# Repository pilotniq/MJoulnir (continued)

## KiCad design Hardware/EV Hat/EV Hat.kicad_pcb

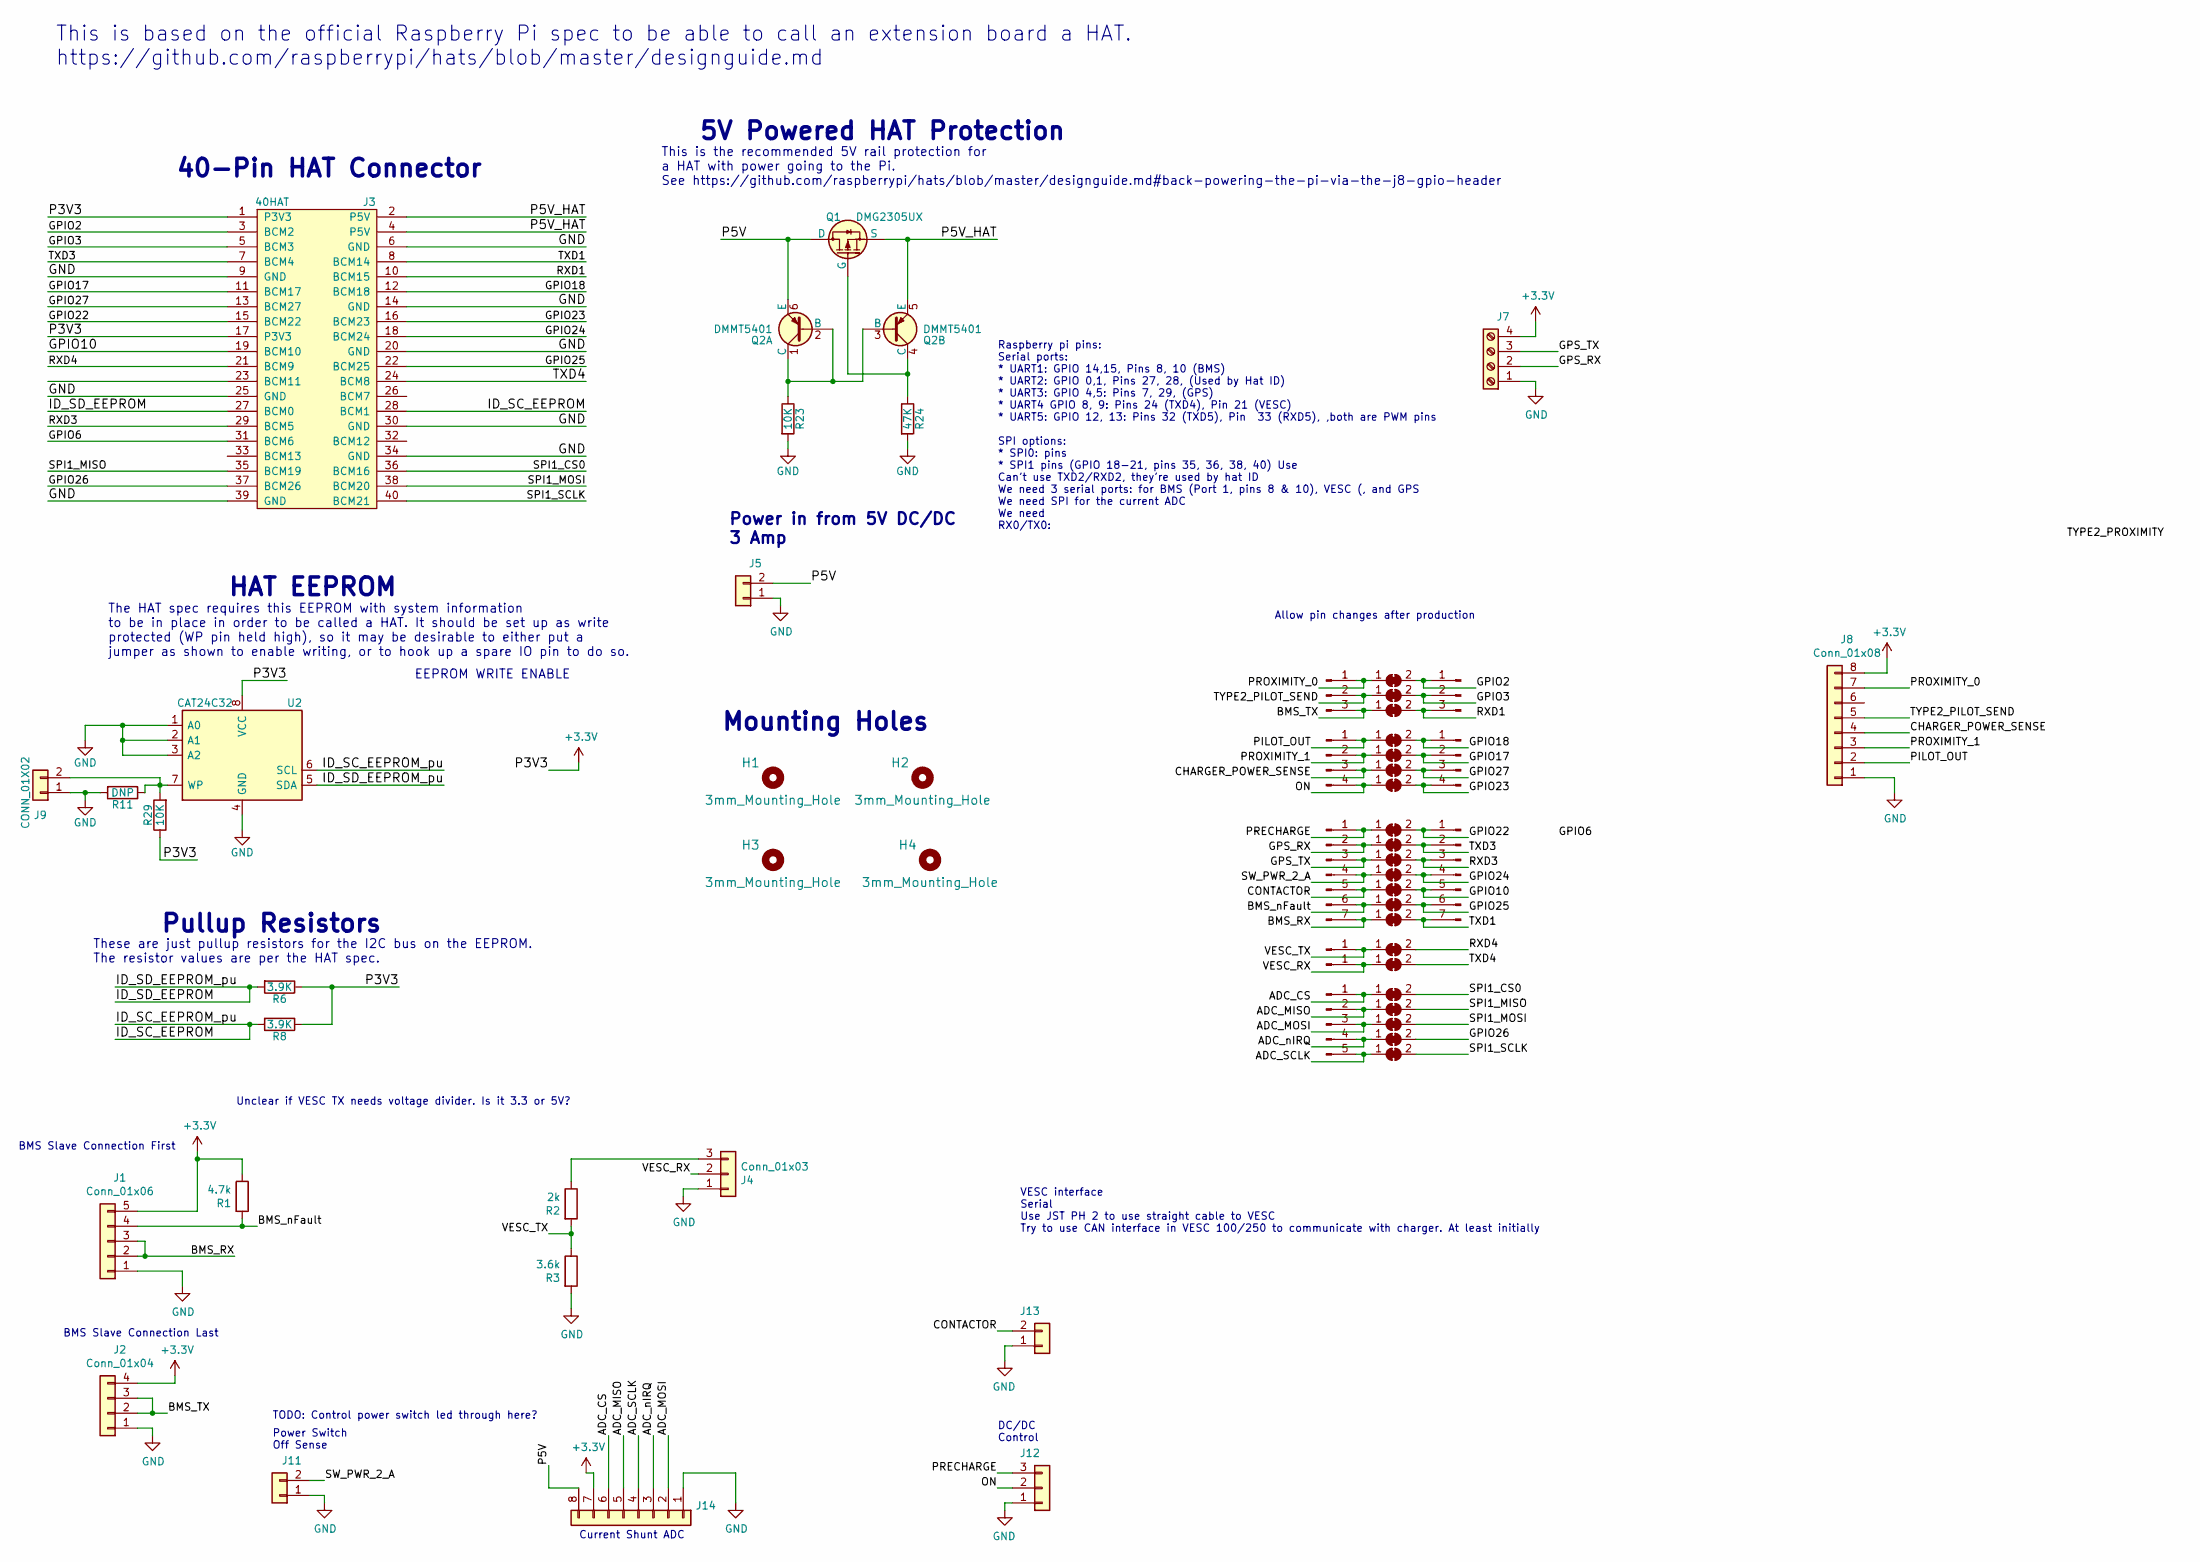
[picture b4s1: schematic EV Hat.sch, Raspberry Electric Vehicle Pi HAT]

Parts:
H1, H2, H3, H4: 3mm_Mounting_Hole; NPTH_3mm_ID
J1: Conn_01x06; CON-MOLEX-CGRIDIII-2x3-0901303206
J2: Conn_01x04; CON-MOLEX-CGRIDIII-1x4-0901361204
J3: 40HAT; PinSocket_2x20_P2.54mm_Vertical
J4, J12: Conn_01x03; CON-MOLEX-CGRIDIII-1x3-RA-0901362203
J5, J11, J13: Conn_01x02; CON-MOLEX-CGRIDIII-1x2 RA-0901362202
J6, J18: Conn_01x07_Male; PinHeader_1x07_P2.54mm_Vertical
J7: Screw_Terminal_01x03; CON-MOLEX-CGRIDIII-1x4-RA-0901362204
J8: Conn_01x08; CON-MOLEX-CGRIDIII-2x4-RA-0901303208
J9: CONN_01X02; PinHeader_1x02_P2.54mm_Vertical
J10, J15: Conn_01x03_Male; PinHeader_1x03_P2.54mm_Vertical
J14: Conn_01x07; CON-MOLEX-CGRIDIII-2x4-RA-0901303208
J16, J17: Conn_01x04_Male; PinHeader_1x04_P2.54mm_Vertical
J19: Conn_01x04_Male; PinHeader_1x05_P2.54mm_Vertical
J20, J21: Conn_01x01_Male; PinHeader_1x01_P2.54mm_Vertical
JP1, JP2, JP3, JP4, JP5, JP6, JP7, JP8, JP9, JP10, JP11, JP12, JP13, JP14, JP15, JP16, JP17, JP18, JP19, JP20, JP21: SolderJumper_2_Bridged; SolderJumper-2_P1.3mm_Bridged_RoundedPad1.0x1.5mm
Q1: DMG2305UX; SOT-23
Q2: DMMT5401; SOT-23-6
R1: 4.7k; R_0603_1608Metric_Pad1.05x0.95mm_HandSolder
R2: 2k; R_0603_1608Metric_Pad1.05x0.95mm_HandSolder
R3: 3.6k; R_0603_1608Metric_Pad1.05x0.95mm_HandSolder
R6, R8: 3.9K; R_0603_1608Metric_Pad0.84x1.00mm_HandSolder
R11: DNP; R_0603_1608Metric_Pad0.84x1.00mm_HandSolder
R23, R29: 10K; R_0603_1608Metric_Pad0.84x1.00mm_HandSolder
R24: 47K; R_0603_1608Metric_Pad0.84x1.00mm_HandSolder
U2: CAT24C32; SOIC-8_3.9x4.9mm_P1.27mm

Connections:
+3V3: J1.5, J2.4, J3.1 (P3V3), J3.17 (P3V3), J7.4, J8.8, J14.7, R1.1, R6.1, R8.1, R29.1, U2.8 (VCC)
/ADC_CS: J14.6, J19.1, JP15.1 (A)
/ADC_MISO: J14.5, J19.2, JP16.1 (A)
/ADC_MOSI: J14.2, J19.3, JP17.1 (A)
/ADC_SCLK: J14.4, J19.5, JP19.1 (A)
/ADC_nIRQ: J14.3, J19.4, JP18.1 (A)
/BMS_RX: J1.2, J1.3, J6.7, JP14.1 (A)
/BMS_TX: J2.2, J2.3, J10.3, JP4.1 (A)
/BMS_nFault: J1.4, J6.6, JP13.1 (A), R1.2
/CHARGER_POWER_SENSE: J8.4, J16.3, JP7.1 (A)
/CONTACTOR: J6.5, J13.2, JP12.1 (A)
/GPIO2: J3.3 (BCM2), J15.1, JP1.2 (B)
/GPIO3: J3.5 (BCM3), J15.2, JP2.2 (B)
/GPIO10: J3.19 (BCM10), J18.5, JP12.2 (B)
/GPIO17: J3.11 (BCM17), J17.2, JP6.2 (B)
/GPIO18: J3.12 (BCM18), J17.1, JP5.2 (B)
/GPIO22: J3.15 (BCM22), J18.1, JP3.2 (B)
/GPIO23: J3.16 (BCM23), J17.4, JP8.2 (B)
/GPIO24: J3.18 (BCM24), J18.4, JP11.2 (B)
/GPIO25: J3.22 (BCM25), J18.6, JP13.2 (B)
/GPIO26: J3.37 (BCM26), JP18.2 (B)
/GPIO27: J3.13 (BCM27), J17.3, JP7.2 (B)
/GPS_RX: J6.2, J7.2, JP9.1 (A)
/GPS_TX: J6.3, J7.3, JP10.1 (A)
/ID_SC_EEPROM: J3.28 (BCM1), R8.2, U2.6 (SCL)
/ID_SD_EEPROM: J3.27 (BCM0), R6.2, U2.5 (SDA)
/ON: J12.2, J16.4, JP8.1 (A)
/P5V: J5.2, J14.8, Q1.3 (D), Q2.6 (E)
/P5V_HAT: J3.2 (P5V), J3.4 (P5V), Q1.2 (S), Q2.5 (E)
/PILOT_OUT: J8.2, J16.1, JP5.1 (A)
/PRECHARGE: J6.1, J12.3, JP3.1 (A)
/PROXIMITY_0: J8.7, J10.1, JP1.1 (A)
/PROXIMITY_1: J8.3, J16.2, JP6.1 (A)
/RXD1: J3.10 (BCM15), J15.3, JP4.2 (B)
/RXD3: J3.29 (BCM5), J18.3, JP10.2 (B)
/RXD4: J3.21 (BCM9), JP20.2 (B)
/SPI1_CS0: J3.36 (BCM16), JP15.2 (B)
/SPI1_MISO: J3.35 (BCM19), JP16.2 (B)
/SPI1_MOSI: J3.38 (BCM20), JP17.2 (B)
/SPI1_SCLK: J3.40 (BCM21), JP19.2 (B)
/SW_PWR_2_A: J6.4, J11.2, JP11.1 (A)
/TXD1: J3.8 (BCM14), J18.7, JP14.2 (B)
/TXD3: J3.7 (BCM4), J18.2, JP9.2 (B)
/TXD4: J3.24 (BCM8), JP21.2 (B)
/TYPE2_PILOT_SEND: J8.5, J10.2, JP2.1 (A)
/VESC_RX: J4.2, J21.1, JP21.1 (A)
/VESC_TX: J20.1, JP20.1 (A), R2.2, R3.1
GND: J1.1, J2.1, J3.6 (GND), J3.9 (GND), J3.14 (GND), J3.20 (GND), J3.25 (GND), J3.30 (GND), J3.34 (GND), J3.39 (GND), J4.1, J5.1, J7.1, J8.1, J9.1, J11.1, J12.1, J13.1, J14.1, R3.2, R11.2, R23.2, R24.2, U2.1 (A0), U2.2 (A1), U2.3 (A2), U2.4 (GND)
unnamed: J4.3, R2.1
unnamed: J9.2, R11.1, R29.2, U2.7 (WP)
unnamed: Q1.1 (G), Q2.4 (C), R24.1
unnamed: Q2.1 (C), Q2.2 (B), Q2.3 (B), R23.1

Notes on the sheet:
5V Powered HAT Protection
This is the recommended 5V rail protection for a HAT with power going to the Pi. See https://github.com/raspberrypi/hats/blob/master/designguide.md#back-powering-the-pi-via-the-j8-gpio-header
EEPROM WRITE ENABLE
Pullup Resistors
HAT EEPROM
Mounting Holes
40-Pin HAT Connector
The HAT spec requires this EEPROM with system information to be in place in order to be called a HAT. It should be set up as write protected (WP pin held high), so it may be desirable to either put a jumper as shown to enable writing, or to hook up a spare IO pin to do so.
These are just pullup resistors for the I2C bus on the EEPROM. The resistor values are per the HAT spec.
This is based on the official Raspberry Pi spec to be able to call an extension board a HAT. https://github.com/raspberrypi/hats/blob/master/designguide.md
BMS Slave Connection First
BMS Slave Connection Last
VESC interface Serial Use JST PH 2 to use straight cable to VESC Try to use CAN interface in VESC 100/250 to communicate with charger. At least initially
Unclear if VESC TX needs voltage divider. Is it 3.3 or 5V?
Power in from 5V DC/DC 3 Amp
Power Switch Off Sense
DC/DC Control
Current Shunt ADC
Raspberry pi pins: Serial ports: * UART1: GPIO 14,15, Pins 8, 10 (BMS) * UART2: GPIO 0,1, Pins 27, 28, (Used by Hat ID) * UART3: GPIO 4,5: Pins 7, 29, (GPS) * UART4 GPIO 8, 9: Pins 24 (TXD4), Pin 21 (VESC) * UART5: GPIO 12, 13: Pins 32 (TXD5), Pin 33 (RXD5), ,both are PWM pins SPI options: * SPI0: 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
Allow pin changes after production
TODO: Control power switch led through here?

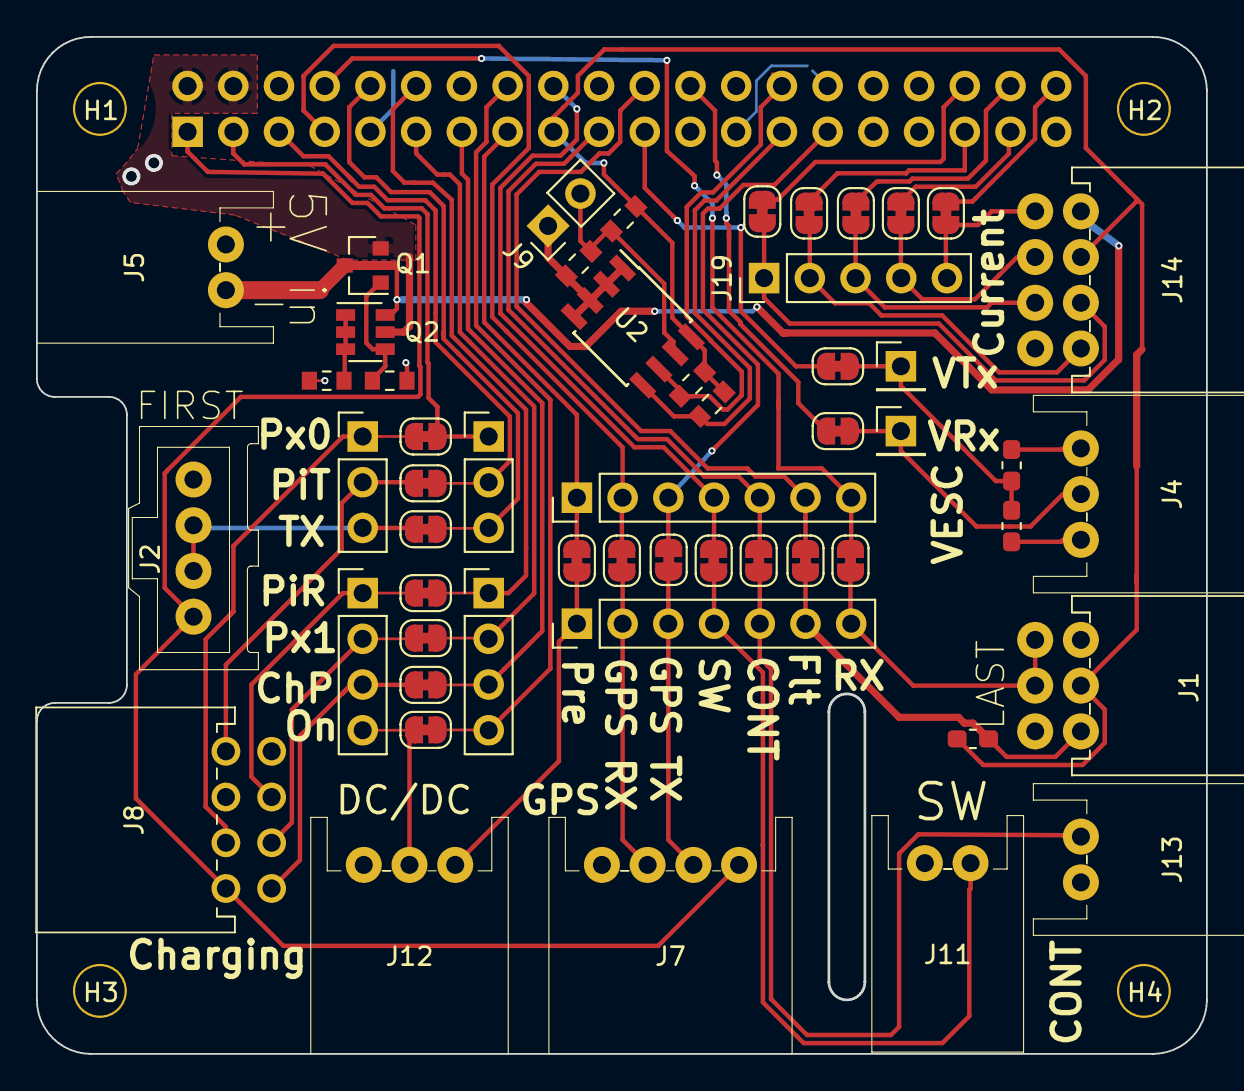
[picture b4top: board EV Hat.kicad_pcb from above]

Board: 2 copper layers, 65.0 x 56.5 mm, 58 parts (1 on the bottom side), 52 nets.

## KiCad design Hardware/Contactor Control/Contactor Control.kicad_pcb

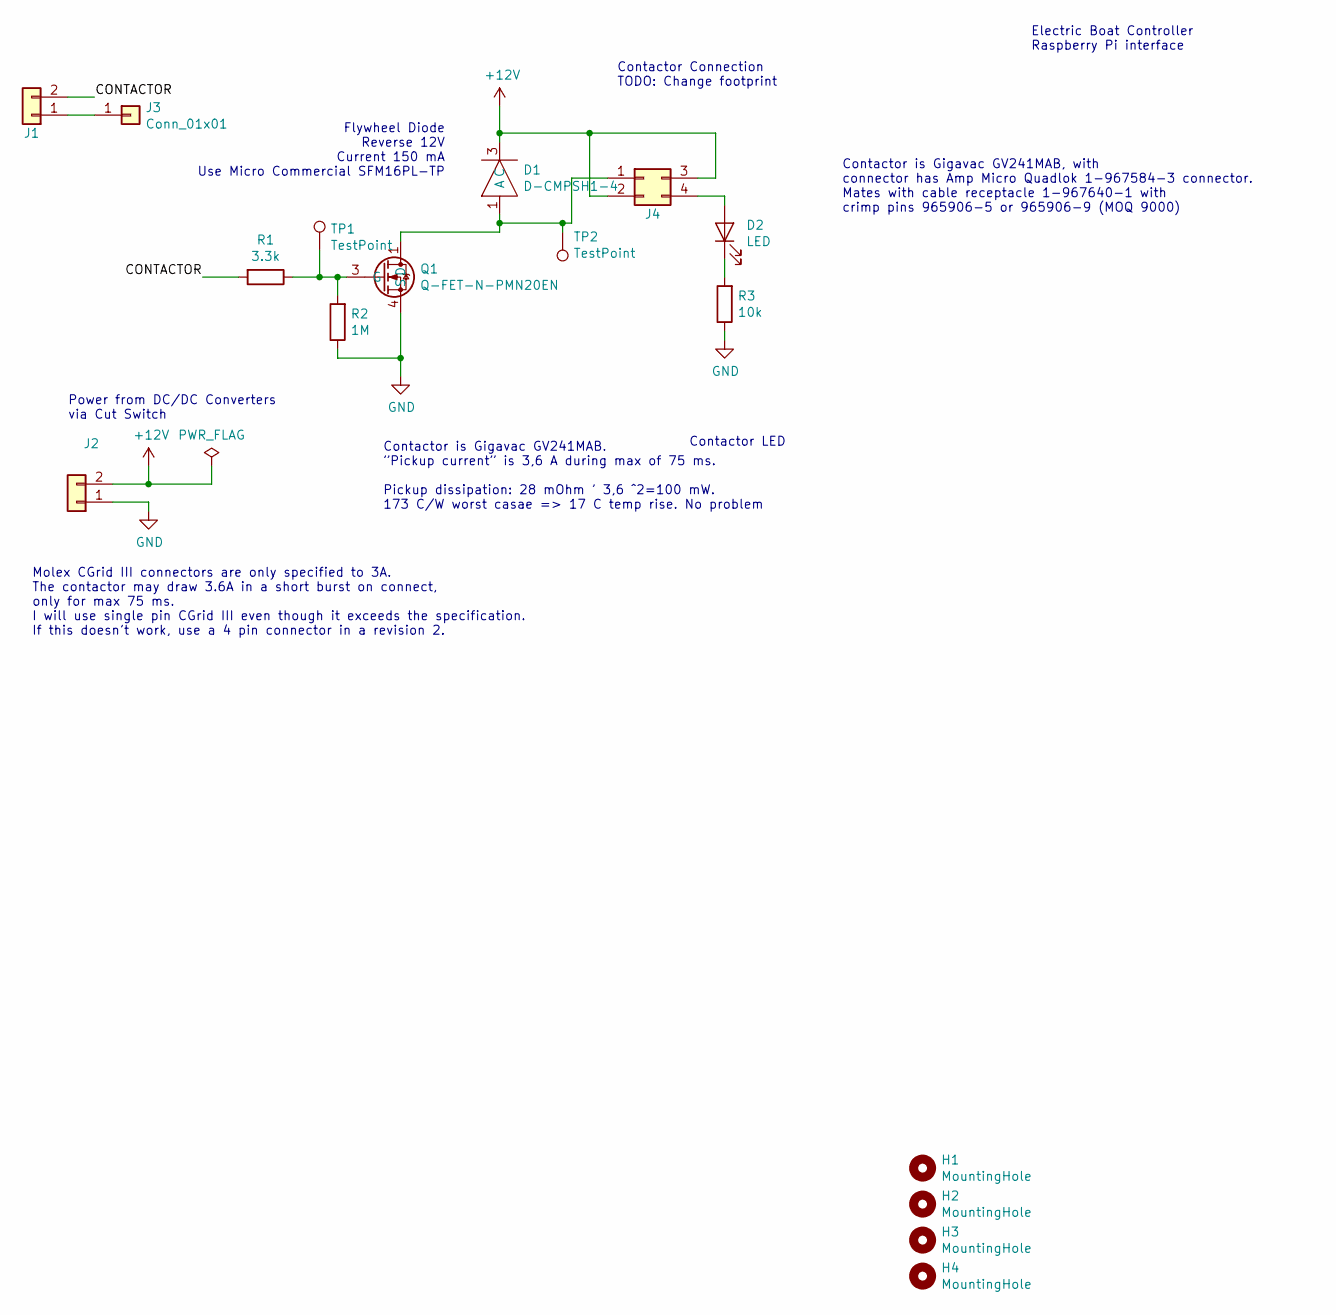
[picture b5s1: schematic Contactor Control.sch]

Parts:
D1: D-CMPSH1-4; SOT23F
D2: LED; LED_0603_1608Metric_Pad1.05x0.95mm_HandSolder
H1, H2, H3, H4: MountingHole; MountingHole_4.3mm_M4_ISO14580
J1, J2: Conn_01x02; CON-MOLEX-CGRIDIII-1x2 RA-0901362202
J3: Conn_01x01; SolderWirePad_1x01_Drill1mm
J4: Conn_02x02_Top_Bottom; CON-MOLEX-CGRIDIII-1x4-RA-0901362204
Q1: Q-FET-N-PMN20EN; TSOP-6_1.65x3.05mm_P0.95mm
R1: 3.3k; R_0603_1608Metric_Pad1.05x0.95mm_HandSolder
R2: 1M; R_0603_1608Metric_Pad1.05x0.95mm_HandSolder
R3: 10k; R_0603_1608Metric_Pad1.05x0.95mm_HandSolder
TP1, TP2: TestPoint; TestPoint_Pad_D2.0mm

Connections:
+12V: D1.3 (C), J2.2, J4.2, J4.3
/CONTACTOR: J1.2, R1.2
GND: J2.1, Q1.4 (S), R2.1, R3.1
unnamed: D1.1 (A), J4.1, Q1.1 (D), Q1.2 (D), Q1.5 (D), Q1.6 (D), TP2.1
unnamed: D2.1 (K), R3.2
unnamed: D2.2 (A), J4.4
unnamed: J1.1, J3.1
unnamed: Q1.3 (G), R1.1, R2.2, TP1.1

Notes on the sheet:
Electric Boat Controller Raspberry Pi interface
Contactor Connection TODO: Change footprint
Power from DC/DC Converters via Cut Switch
Contactor LED
Flywheel Diode Reverse 12V Current 150 mA Use Micro Commercial SFM16PL-TP
Contactor is Gigavac GV241MAB. ”Pickup current” is 3,6 A during max of 75 ms. Pickup dissipation: 28 mOhm ’ 3,6 ^2=100 mW. 173 C/W worst casae => 17 C temp rise. No problem
Molex CGrid III connectors are only specified to 3A. The contactor may draw 3.6A in a short burst on connect, only for max 75 ms. I will use single pin CGrid III even though it exceeds the specification. If this doesn’t work, use a 4 pin connector in a revision 2.
Contactor is Gigavac GV241MAB, with connector has Amp Micro Quadlok 1-967584-3 connector. Mates with cable receptacle 1-967640-1 with crimp pins 965906-5 or 965906-9 (MOQ 9000)

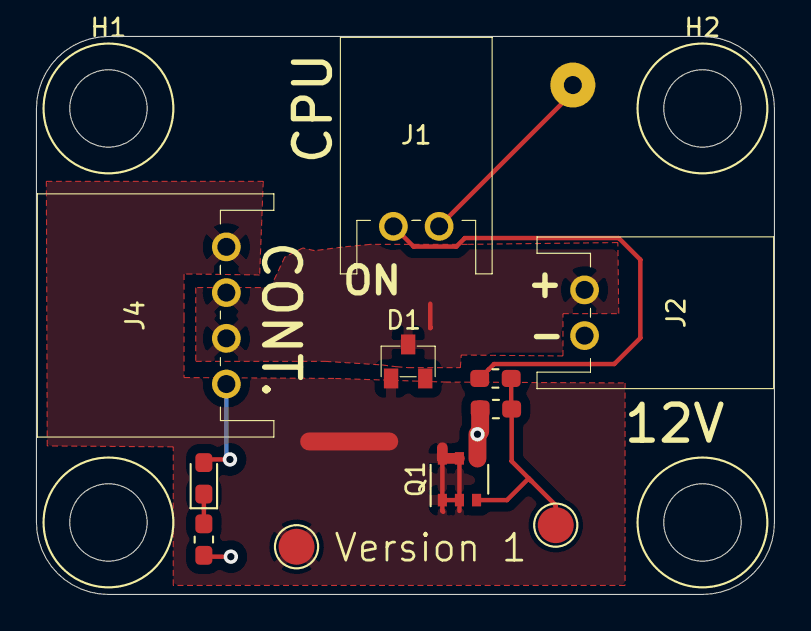
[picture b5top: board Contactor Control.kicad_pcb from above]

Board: 2 copper layers, 41.0 x 31.0 mm, 16 parts (0 on the bottom side), 8 nets.

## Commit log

2021-01-31 Revision 2 of the DCDC Control PCB.
    Now with precharge for both DC/DC and VESC, 150 ohm 45 W precharge resistors
    (up to three per device).
    Microcontroller to control the sequencing. ADC measurement of in vs out voltage
    to determine when precharge is complete.
2021-02-23 Added scripts for controlling precharge & contactor
2021-02-23 Added simple scripts to read out Tesla battery module BMS slave data
2021-04-15 Continued work
2021-04-15 Raspberry Pi DeviceTree stuff
2021-05-03 Added scripts for setting up reverse ssh tunnel when WiFi is connected
2021-05-08 Added iOS App
2021-05-08 Started refactoring to be able to run with simulated hardware for testing Added Active state Fixed support for displaying power and energy in App.
2021-05-14 Continue work on simulation, and active state
2021-05-16 Continued work in boat to get it working again.
2021-05-16 Continued App work
2021-05-16 Fix updating battery model current when new vesc data comes
2021-05-16 Bug fixes
2021-05-22 Removed Booting state, added Arming state
2021-05-23 Work on simulation and charging
2021-05-23 Work on charging
2021-06-03 Reconstruct files lost in SD card crash
2021-06-04 Continued work restoring sw, web interface and charging mode
2021-06-06 Changs mostly related to charging made on the boat. Limit derating of battery charging current relate to tempereture when just above 30 C
2021-06-21 Work on simulation and charging. Added Charger Settings BLE attribute.
2021-06-21 Work on Charging screen of app Support ChargingSettings BLE Characteristic
2021-07-03 Split BLE charger settings characteristics into separate characteristics for max wall current and target SOC
2021-07-03 Work on charging settings and segues
2021-07-03 Fix segue dismissing
2021-07-03 Older PCB updates
2021-07-03 Add VESC heading in simulator web page
2021-07-03 Ignore xcuserdata
2021-07-03 gitignore 2
2022-05-02 Added reading battery fault line in scripts
2022-07-24 Add some logging to batteryReader
2022-07-24 Add support for autodetecting number of serial cells, started work on state to turn Raspberry Pi off
2022-07-24 Started adding support for throttle control from Pi
2022-07-24 Added charging params to armed state view
2023-05-21 Document system changes for networking (WiFi, 3G)
2023-05-21 WIP work to read AppConf from VESC (to later be able to change App, to be able to control throttle by SW
2024-05-26 Add HTTP REST API
2024-05-26 start adding MQTT support
2024-05-26 Allow arming to charge at low battery voltage. Don't go to active if duty cycle is below 0.5%.
2024-05-26 Add reading AppConf from VESC, in preparation for switching input source
2024-05-26 Modify wifiTunnel.service to run reverse SSH tunnel after wvdial.service
2024-05-26 Change BMS-slave communication to run at 631578 bps
2024-05-26 Fix bug where charging would continue into balancing
2024-05-26 Add scripts to get info from HTTP REST API
